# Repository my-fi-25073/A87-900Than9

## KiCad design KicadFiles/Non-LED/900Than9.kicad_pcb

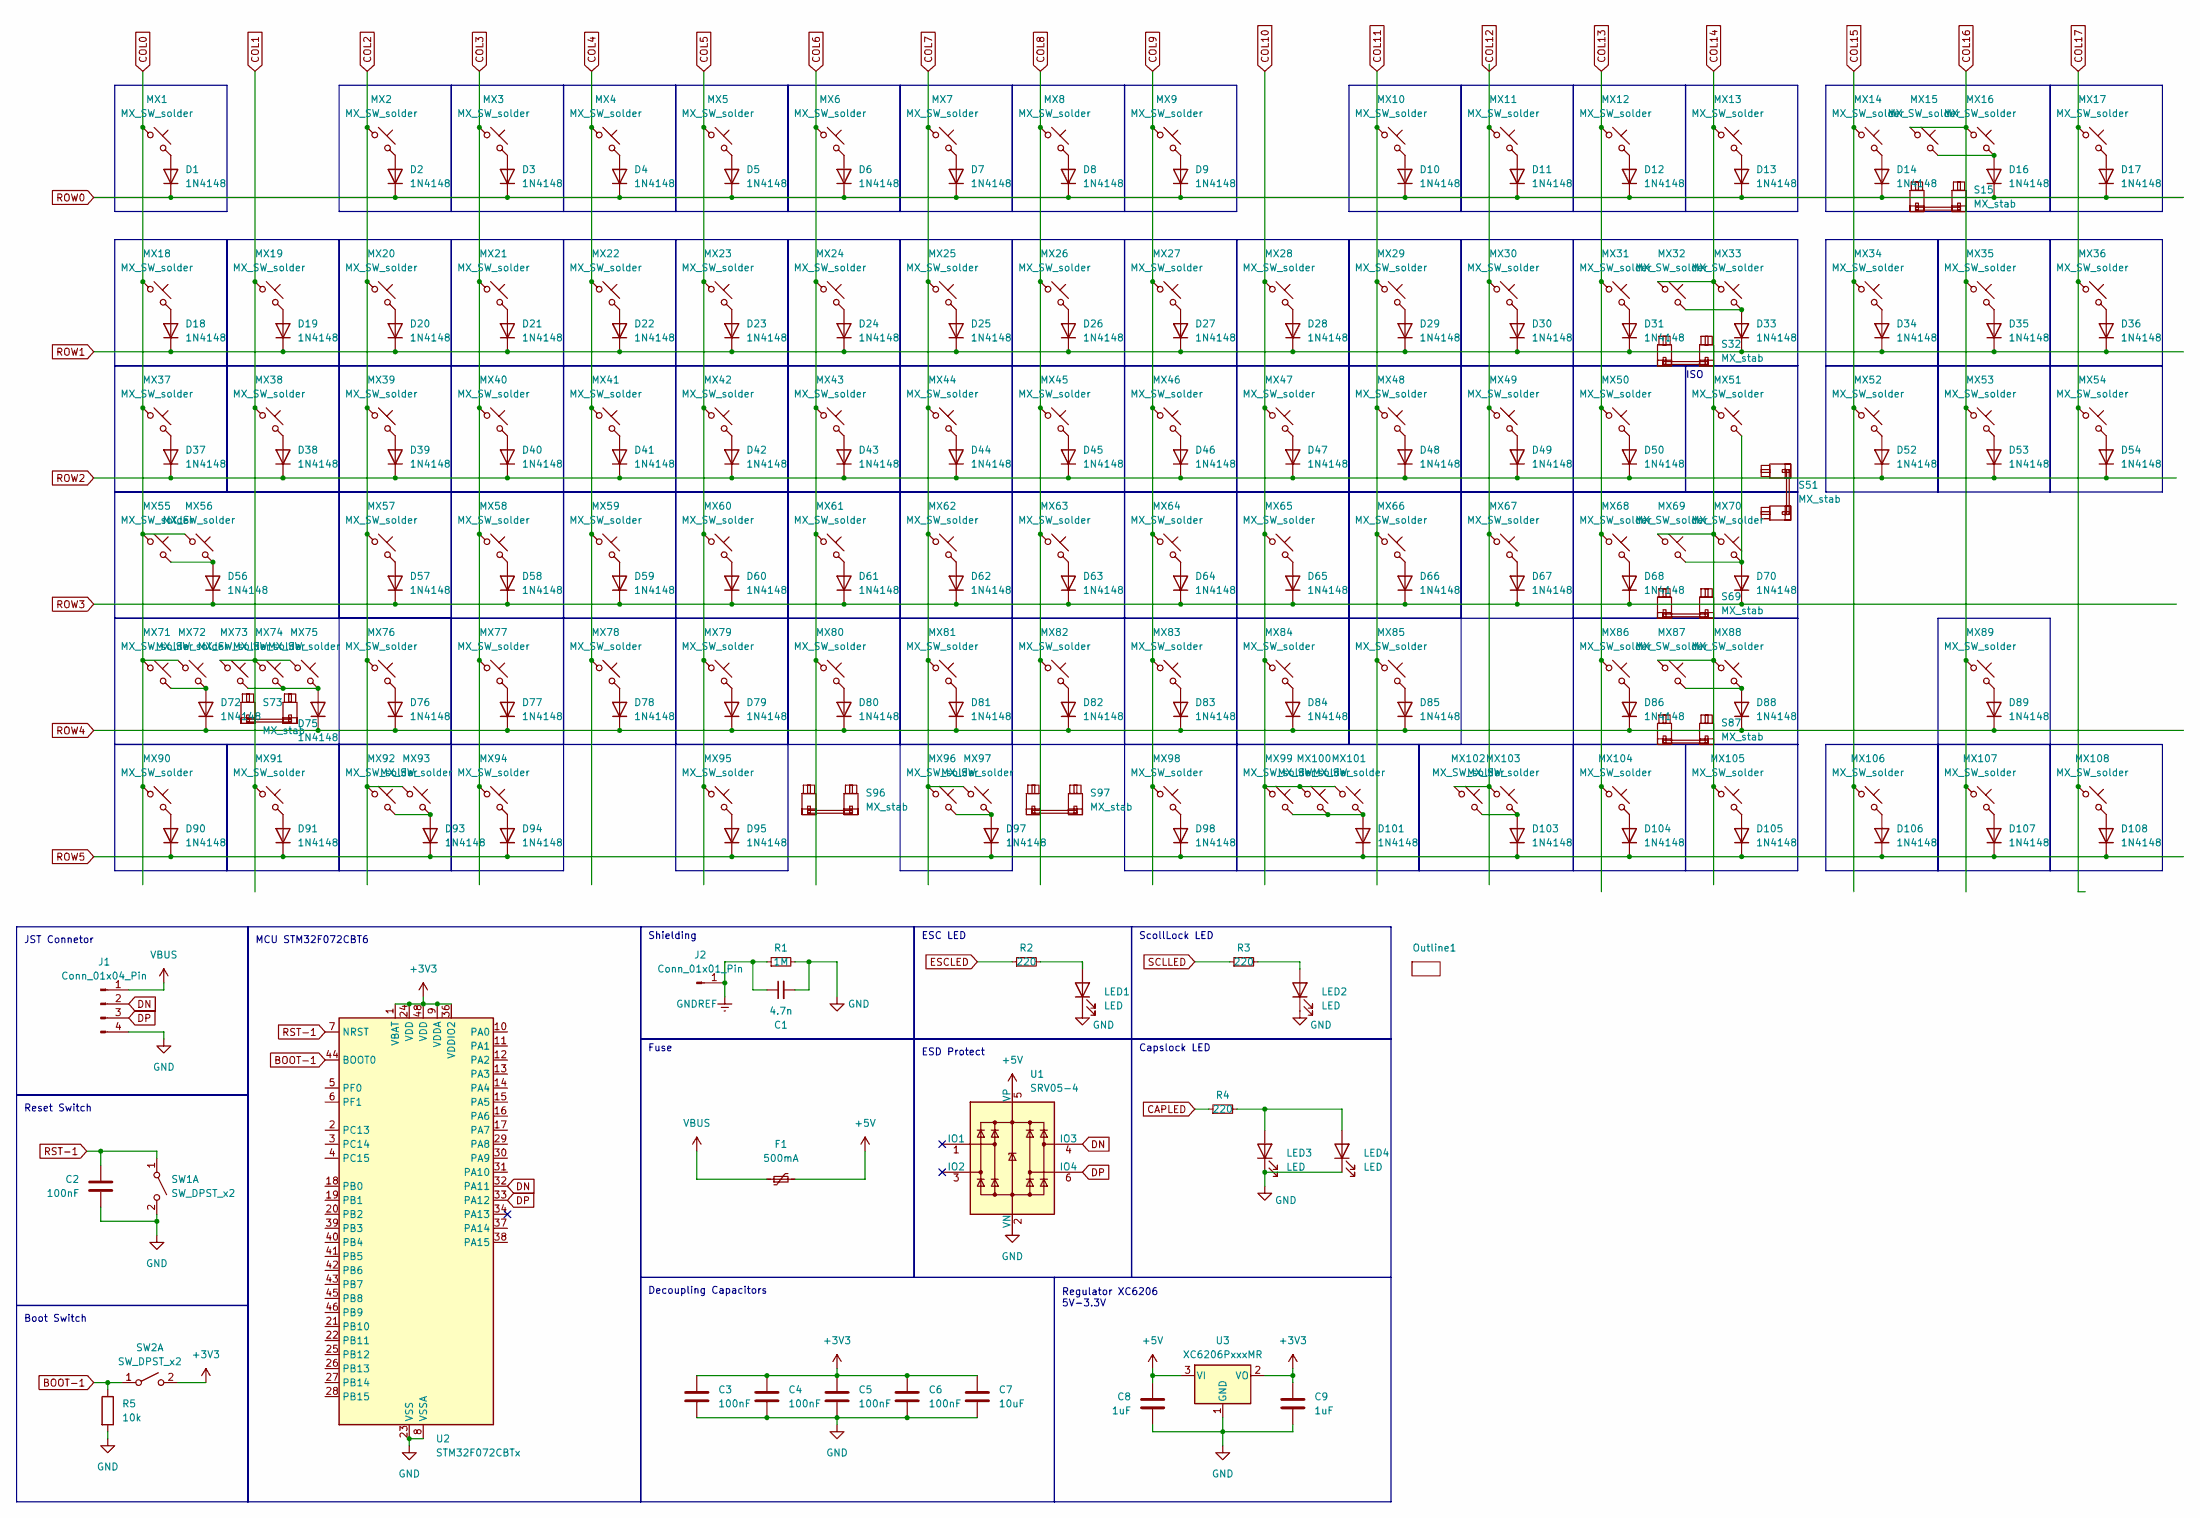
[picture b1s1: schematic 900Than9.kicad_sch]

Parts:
C1: 4.7n; C_0402_1005Metric
C2, C3, C4, C5, C6: 100nF; C_0402_1005Metric
C7: 10uF; C_0402_1005Metric
C8, C9: 1uF; C_0402_1005Metric
D1, D2, D3, D4, D5, D6, D7, D8, D9, D10, D11, D12, D13, D14, D16, D17, D18, D19, D20, D21, D22, D23, D24, D25, D26, D27, D28, D29, D30, D31, D33, D34, D35, D36, D37, D38, D39, D40, D41, D42, D43, D44, D45, D46, D47, D48, D49, D50, D52, D53, D54, D56, D57, D58, D59, D60, D61, D62, D63, D64, D65, D66, D67, D68, D70, D72, D75, D76, D77, D78, D79, D80, D81, D82, D83, D84, D85, D86, D88, D89, D90, D91, D93, D94, D95, D97, D98, D101, D103, D104, D105, D106, D107, D108: 1N4148; D_SOD-323_HandSoldering
F1: 500mA; Fuse_1206_3216Metric; LCSC C70076
J1: Conn_01x04_Pin; JST_SH_SM04B-SRSS-TB_1x04-1MP_P1.00mm_Horizontal; MPN C160404
J2: Conn_01x01_Pin; TestPoint_THTPad_2.0x2.0mm_Drill1.0mm
LED1, LED2, LED4: LED; DIP_LED_MX_3mm
LED3: LED; CAPS_LED_MX_3mm
MX1, MX2, MX3, MX4, MX5, MX6, MX7, MX8, MX9, MX10, MX11, MX12, MX13, MX14, MX15, MX16, MX17, MX18, MX19, MX20, MX21, MX22, MX23, MX24, MX25, MX26, MX27, MX28, MX29, MX30, MX31, MX32, MX33, MX34, MX35, MX36, MX38, MX39, MX40, MX41, MX42, MX43, MX44, MX45, MX46, MX47, MX48, MX49, MX51, MX52, MX53, MX54, MX57, MX58, MX59, MX60, MX61, MX62, MX63, MX64, MX65, MX66, MX67, MX68, MX69, MX71, MX73, MX75, MX76, MX77, MX78, MX79, MX80, MX81, MX82, MX83, MX84, MX85, MX87, MX88, MX89, MX91, MX92, MX94, MX95, MX96, MX97, MX98, MX99, MX101, MX103, MX104, MX106, MX107, MX108: MX_SW_solder; SW_MX_1u
MX37, MX50, MX90, MX93, MX100, MX102, MX105: MX_SW_solder; SW_MX_1.5u
MX55: MX_SW_solder; SW_MX_1.75u_STP_1.25
MX56, MX86: MX_SW_solder; SW_MX_1.75u
MX70, MX72, MX74: MX_SW_solder; SW_MX_1.25u
Outline1: A87-outline_jst
R1: 1M; R_0402_1005Metric
R2, R3, R4: 220; R_0402_1005Metric
R5: 10k; R_0402_1005Metric
S15, S32: MX_stab; STAB_MX_2u
S51: MX_stab; STAB_MX_ISO-ROT
S69, S73: MX_stab; STAB_MX_2.25u
S87: MX_stab; STAB_MX_2.75u
S96: MX_stab; STAB_MX_6u
S97: MX_stab; STAB_MX_6u_7u_313u
SW1, SW2: SW_DPST_x2; SW_Push_1P1T_XKB_TS-1187A; MPN C318884
U1: SRV05-4; SOT-23-6; MPN C7420376
U2: STM32F072CBTx; LQFP-48_7x7mm_P0.5mm; MPN C81720
U3: XC6206PxxxMR; SOT-23-3; MPN C5148692

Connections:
+3V3: C3.1, C4.1, C5.1, C6.1, C7.1, C9.1, SW2.2 (B), U2.1 (VBAT), U2.9 (VDDA), U2.24 (VDD), U2.36 (VDDIO2), U2.48 (VDD), U3.2 (VO)
+5V: C8.1, F1.2, U1.5 (VP), U3.3 (VI)
BOOT-1: R5.1, SW2.1 (A), U2.44 (BOOT0)
CAPLED: R4.1
COL0: MX1.1, MX18.1, MX37.1, MX55.1, MX56.1, MX71.1, MX72.1, MX90.1
COL1: MX19.1, MX38.1, MX73.1, MX74.1, MX75.1, MX91.1
COL2: MX2.1, MX20.1, MX39.1, MX57.1, MX76.1, MX92.1, MX93.1
COL3: MX3.1, MX21.1, MX40.1, MX58.1, MX77.1, MX94.1
COL4: MX4.1, MX22.1, MX41.1, MX59.1, MX78.1
COL5: MX5.1, MX23.1, MX42.1, MX60.1, MX79.1, MX95.1
COL6: MX6.1, MX24.1, MX43.1, MX61.1, MX80.1
COL7: MX7.1, MX25.1, MX44.1, MX62.1, MX81.1, MX96.1, MX97.1
COL8: MX8.1, MX26.1, MX45.1, MX63.1, MX82.1
COL9: MX9.1, MX27.1, MX46.1, MX64.1, MX83.1, MX98.1
COL10: MX28.1, MX47.1, MX65.1, MX84.1, MX99.1, MX100.1, MX101.1
COL11: MX10.1, MX29.1, MX48.1, MX66.1, MX85.1
COL12: MX11.1, MX30.1, MX49.1, MX67.1, MX102.1, MX103.1
COL13: MX12.1, MX31.1, MX50.1, MX68.1, MX86.1, MX104.1
COL14: MX13.1, MX32.1, MX33.1, MX51.1, MX69.1, MX70.1, MX87.1, MX88.1, MX105.1
COL15: MX14.1, MX34.1, MX52.1, MX106.1
COL16: MX15.1, MX16.1, MX35.1, MX53.1, MX89.1, MX107.1
COL17: MX17.1, MX36.1, MX54.1, MX108.1
DN: J1.2, U1.4 (IO3), U2.32 (PA11)
DP: J1.3, U1.6 (IO4), U2.33 (PA12)
ESCLED: R2.1
GND: C1.2, C2.2, C3.2, C4.2, C5.2, C6.2, C7.2, C8.2, C9.2, J1.4, LED1.1 (K), LED2.1 (K), LED3.1 (K), LED4.1 (K), R1.2, R5.2, SW1.2 (B), U1.2 (VN), U2.8 (VSSA), U2.23 (VSS), U2.35 (VSS), U2.47 (VSS), U3.1 (GND)
GNDREF: C1.1, J2.1, R1.1
unnamed: D1.2 (A), MX1.2
unnamed: D2.2 (A), MX2.2
unnamed: D3.2 (A), MX3.2
unnamed: D4.2 (A), MX4.2
unnamed: D5.2 (A), MX5.2
unnamed: D6.2 (A), MX6.2
unnamed: D7.2 (A), MX7.2
unnamed: D8.2 (A), MX8.2
unnamed: D9.2 (A), MX9.2
unnamed: D10.2 (A), MX10.2
unnamed: D11.2 (A), MX11.2
unnamed: D12.2 (A), MX12.2
unnamed: D13.2 (A), MX13.2
unnamed: D14.2 (A), MX14.2
unnamed: D16.2 (A), MX15.2, MX16.2
unnamed: D17.2 (A), MX17.2
unnamed: D18.2 (A), MX18.2
unnamed: D19.2 (A), MX19.2
unnamed: D20.2 (A), MX20.2
unnamed: D21.2 (A), MX21.2
unnamed: D22.2 (A), MX22.2
unnamed: D23.2 (A), MX23.2
unnamed: D24.2 (A), MX24.2
unnamed: D25.2 (A), MX25.2
unnamed: D26.2 (A), MX26.2
unnamed: D27.2 (A), MX27.2
unnamed: D28.2 (A), MX28.2
unnamed: D29.2 (A), MX29.2
unnamed: D30.2 (A), MX30.2
unnamed: D31.2 (A), MX31.2
unnamed: D33.2 (A), MX32.2, MX33.2
unnamed: D34.2 (A), MX34.2
unnamed: D35.2 (A), MX35.2
unnamed: D36.2 (A), MX36.2
unnamed: D37.2 (A), MX37.2
unnamed: D38.2 (A), MX38.2
unnamed: D39.2 (A), MX39.2
unnamed: D40.2 (A), MX40.2
unnamed: D41.2 (A), MX41.2
unnamed: D42.2 (A), MX42.2
unnamed: D43.2 (A), MX43.2
unnamed: D44.2 (A), MX44.2
unnamed: D45.2 (A), MX45.2
unnamed: D46.2 (A), MX46.2
unnamed: D47.2 (A), MX47.2
unnamed: D48.2 (A), MX48.2
unnamed: D49.2 (A), MX49.2
unnamed: D50.2 (A), MX50.2
unnamed: D52.2 (A), MX52.2
unnamed: D53.2 (A), MX53.2
unnamed: D54.2 (A), MX54.2
unnamed: D56.2 (A), MX55.2, MX56.2
unnamed: D57.2 (A), MX57.2
unnamed: D58.2 (A), MX58.2
unnamed: D59.2 (A), MX59.2
unnamed: D60.2 (A), MX60.2
unnamed: D61.2 (A), MX61.2
unnamed: D62.2 (A), MX62.2
unnamed: D63.2 (A), MX63.2
unnamed: D64.2 (A), MX64.2
unnamed: D65.2 (A), MX65.2
unnamed: D66.2 (A), MX66.2
unnamed: D67.2 (A), MX67.2
unnamed: D68.2 (A), MX68.2
unnamed: D70.2 (A), MX51.2, MX69.2, MX70.2
unnamed: D72.2 (A), MX71.2, MX72.2
unnamed: D75.2 (A), MX73.2, MX74.2, MX75.2
unnamed: D76.2 (A), MX76.2
unnamed: D77.2 (A), MX77.2
unnamed: D78.2 (A), MX78.2
unnamed: D79.2 (A), MX79.2
unnamed: D80.2 (A), MX80.2
unnamed: D81.2 (A), MX81.2
unnamed: D82.2 (A), MX82.2
unnamed: D83.2 (A), MX83.2
unnamed: D84.2 (A), MX84.2
unnamed: D85.2 (A), MX85.2
unnamed: D86.2 (A), MX86.2
unnamed: D88.2 (A), MX87.2, MX88.2
unnamed: D89.2 (A), MX89.2
unnamed: D90.2 (A), MX90.2
unnamed: D91.2 (A), MX91.2
unnamed: D93.2 (A), MX92.2, MX93.2
unnamed: D94.2 (A), MX94.2
unnamed: D95.2 (A), MX95.2
unnamed: D97.2 (A), MX96.2, MX97.2
unnamed: D98.2 (A), MX98.2
unnamed: D101.2 (A), MX99.2, MX100.2, MX101.2
unnamed: D103.2 (A), MX102.2, MX103.2
unnamed: D104.2 (A), MX104.2
unnamed: D105.2 (A), MX105.2
unnamed: D106.2 (A), MX106.2
unnamed: D107.2 (A), MX107.2
unnamed: D108.2 (A), MX108.2
unnamed: LED1.2 (A), R2.2
unnamed: LED2.2 (A), R3.2
unnamed: LED3.2 (A), LED4.2 (A), R4.2
ROW0: D1.1 (K), D2.1 (K), D3.1 (K), D4.1 (K), D5.1 (K), D6.1 (K), D7.1 (K), D8.1 (K), D9.1 (K), D10.1 (K), D11.1 (K), D12.1 (K), D13.1 (K), D14.1 (K), D16.1 (K), D17.1 (K)
ROW1: D18.1 (K), D19.1 (K), D20.1 (K), D21.1 (K), D22.1 (K), D23.1 (K), D24.1 (K), D25.1 (K), D26.1 (K), D27.1 (K), D28.1 (K), D29.1 (K), D30.1 (K), D31.1 (K), D33.1 (K), D34.1 (K), D35.1 (K), D36.1 (K)
ROW2: D37.1 (K), D38.1 (K), D39.1 (K), D40.1 (K), D41.1 (K), D42.1 (K), D43.1 (K), D44.1 (K), D45.1 (K), D46.1 (K), D47.1 (K), D48.1 (K), D49.1 (K), D50.1 (K), D52.1 (K), D53.1 (K), D54.1 (K)
ROW3: D56.1 (K), D57.1 (K), D58.1 (K), D59.1 (K), D60.1 (K), D61.1 (K), D62.1 (K), D63.1 (K), D64.1 (K), D65.1 (K), D66.1 (K), D67.1 (K), D68.1 (K), D70.1 (K)
ROW4: D72.1 (K), D75.1 (K), D76.1 (K), D77.1 (K), D78.1 (K), D79.1 (K), D80.1 (K), D81.1 (K), D82.1 (K), D83.1 (K), D84.1 (K), D85.1 (K), D86.1 (K), D88.1 (K), D89.1 (K)
ROW5: D90.1 (K), D91.1 (K), D93.1 (K), D94.1 (K), D95.1 (K), D97.1 (K), D98.1 (K), D101.1 (K), D103.1 (K), D104.1 (K), D105.1 (K), D106.1 (K), D107.1 (K), D108.1 (K)
RST-1: C2.1, SW1.1 (A), U2.7 (NRST)
SCLLED: R3.1
VBUS: F1.1, J1.1

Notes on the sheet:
Fuse
Reset Switch
MCU STM32F072CBT6
Regulator XC6206 5V-3.3V
Shielding
ScollLock LED
Capslock LED
ESD Protect
ISO
Boot Switch
ESC LED
Decoupling Capacitors
JST Connetor

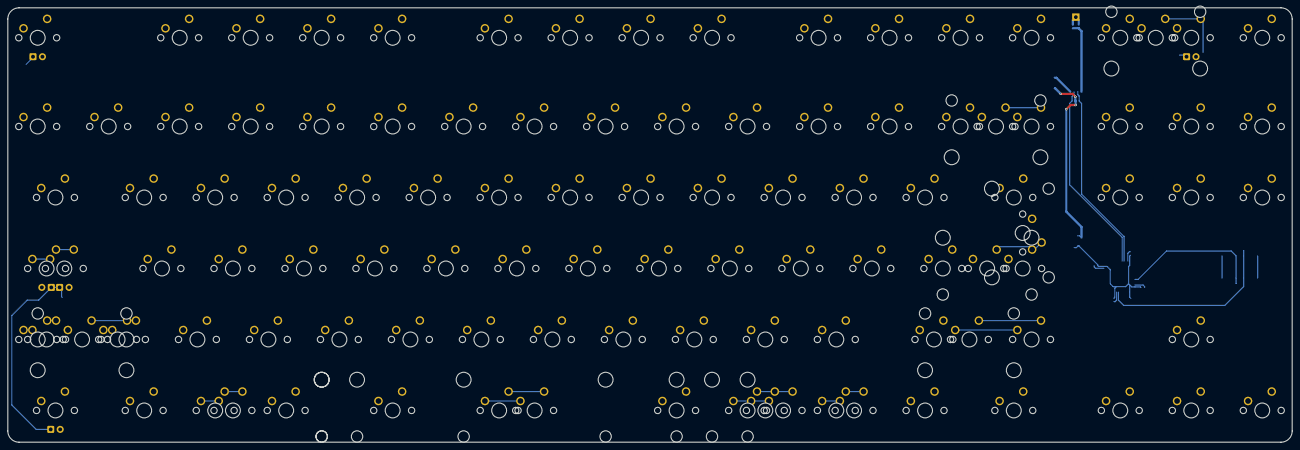
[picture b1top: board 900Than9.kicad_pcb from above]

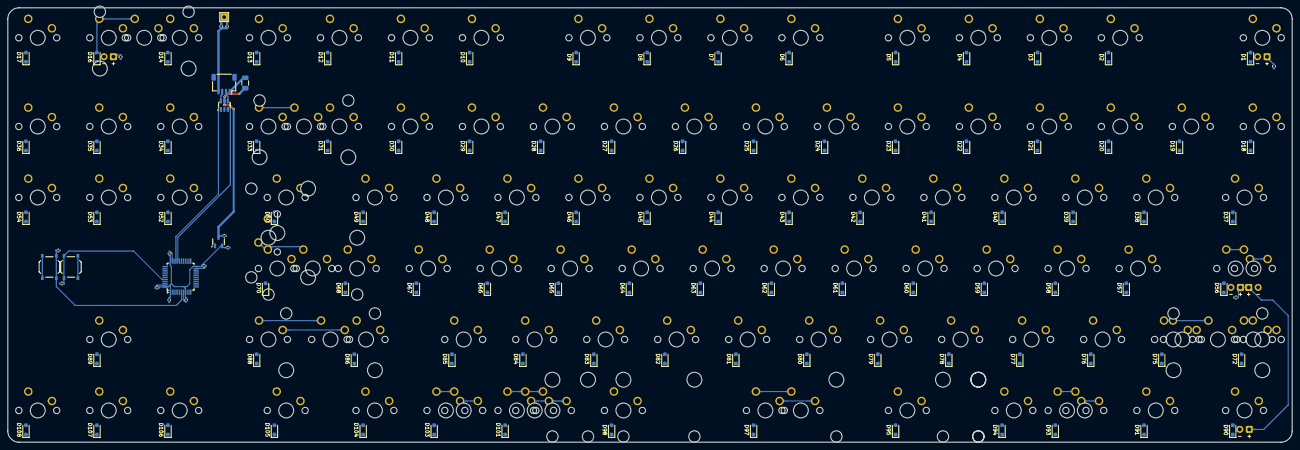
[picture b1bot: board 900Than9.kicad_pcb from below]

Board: 2 copper layers, 344.7 x 116.6 mm, 237 parts (116 on the bottom side), 130 nets.

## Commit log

2025-08-06 Added kidad files...
2025-08-06 Updated LED placement & footprints
2025-08-23 updated pcb & sch
2025-08-24 first version
2025-08-30 Added first version of qmk source codes
2025-08-30 Add configuration files for 900Than9 keyboard with backlight support
2025-08-31 Added LED control and update layout for 900Than9 keyboard
2025-09-22 Added rev2 for 8u space bar.
2025-09-23 adde 5u space bar
2025-09-23 Added rev2
2025-09-30 Updated led functions
2025-09-30 Update LED effects
2025-10-01 Added via menu and apply options using eeprom area
2025-10-02 implement LED control using software timer
2025-10-04 enh: refactor keyboard configuration and effects management
    - Add modular configuration files: my_config.c/h, my_effect.c/h, my_keycode.c/h
    - Add backlight management: my_backlight.c/h
    - Remove legacy myfi.c file
    - Rename myfi.h to my_config.h for better organization
    - Update keymap and configuration files
    - Improve LED effects and configuration management functionality
